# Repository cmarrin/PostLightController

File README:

To send PostLightController board to seeedstudio (https://www.seeedstudio.com/fusion_pcb.html):

	1) open PostLightController.kicad_pcb

	2) go to File->Plot...

	3) Make sure Use Extended X2 Format is not checked

	4) Make sure Output folder is 'gbr/'

	5) Press Plot to generate all the files

	6) Press Generate Drill Files...

	7) Press Generate Drill Files on the sheet that comes up

	8) Go to console in the PostLightController directory and run 'zip PostLightController-gbr.zip gbr/*'

	9) Upload the resulting PostLightController-gbr.zip to SeeedStudio

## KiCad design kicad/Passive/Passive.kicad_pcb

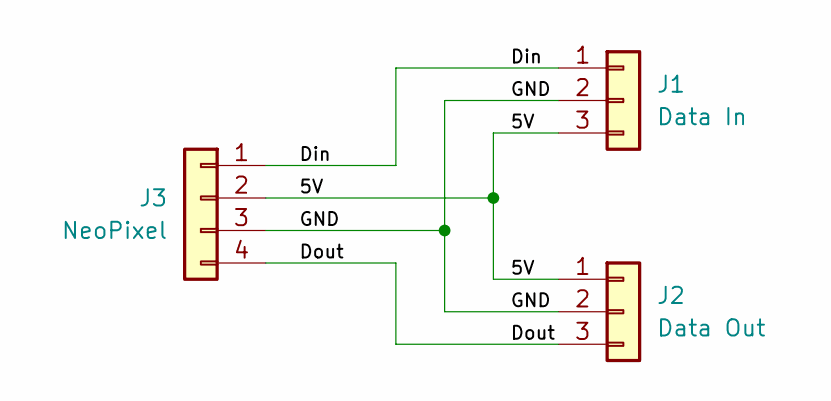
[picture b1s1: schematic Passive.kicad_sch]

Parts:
J1: Data In; PinHeader_1x03_P2.54mm_Horizontal
J2: Data Out; PinHeader_1x03_P2.54mm_Horizontal
J3: NeoPixel; PinHeader_1x04_P2.54mm_Horizontal

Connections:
/5V: J1.3, J2.1, J3.2
/Din: J1.1, J3.1
/Dout: J2.3, J3.4
/GND: J1.2, J2.2, J3.3

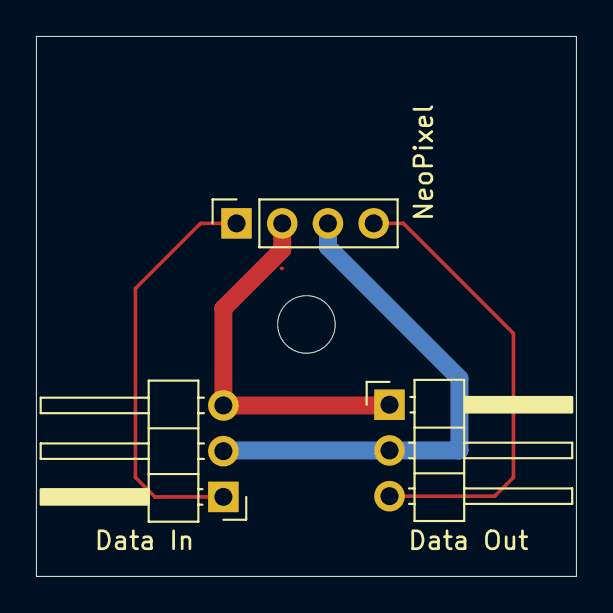
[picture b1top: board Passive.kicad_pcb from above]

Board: 2 copper layers, 30.0 x 30.0 mm, 3 parts (0 on the bottom side), 4 nets.

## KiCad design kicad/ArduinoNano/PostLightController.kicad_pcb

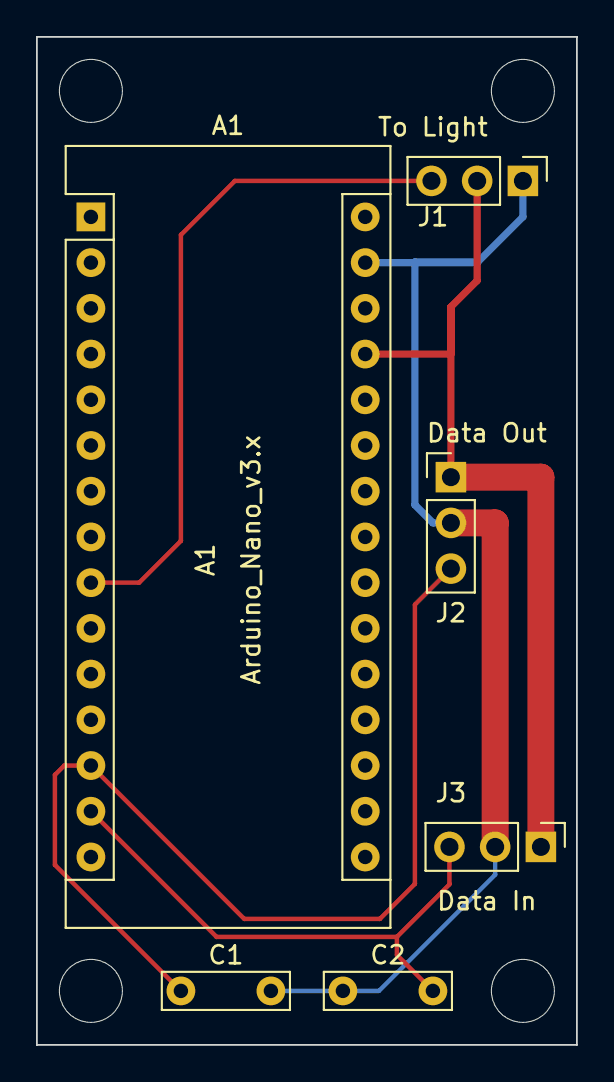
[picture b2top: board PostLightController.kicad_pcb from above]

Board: 2 copper layers, 30.0 x 56.0 mm, 6 parts (0 on the bottom side), 5 nets.

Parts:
A1: Arduino_Nano_v3.x; Arduino_Nano
C1, C2: C; C_Rect_L7.0mm_W2.0mm_P5.00mm
J1: To Light; Pin_Header_Straight_1x03_Pitch2.54mm
J2: Data Out; Pin_Header_Straight_1x03_Pitch2.54mm
J3: Data In; Pin_Header_Straight_1x03_Pitch2.54mm

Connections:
unnamed: A1.9, J1.3
unnamed: A1.13, C1.1, J2.3
unnamed: A1.14, C2.1, J3.3
unnamed: A1.27, J1.2, J2.1, J3.1
unnamed: A1.29, C1.2, C2.2, J1.1, J2.2, J3.2

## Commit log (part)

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2022-01-29 Added scanning of 2 character op sequences for Clover compiler
2022-01-30 Changed Arly syntax
    init and loop keywords are gone. At the end of the file is a lit of effects. As before they have the keyword effect, a single character name and the number of params. But added is an identifier of an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
2022-01-30 Add a Return to the end of functions so they know when to stop
2022-01-30 Renamed LoadIX/StoreIX to LoadDeref/StoreDeref
    This is in preparation for replacing all the indexed instructions with LoadRef/LoadDeref/StoreDeref.
2022-01-30 Got rid of unused OpParams
2022-02-01 Changed LoadParam call to use Rd rather than R
    There's no reason to put the LoadParam register in the lower 2 bits. You need the extra byte anyway, so just moving it there.
2022-02-01 Added unary inc and dec, for later use
2022-02-01 Minor updates to Clover source file
2022-02-01 Added documentation for RAM and Temp sizes in executable
2022-02-02 Added ability to ignore newlines in Scanner
2022-02-03 Fixed lights not coming on in Flicker
    Wasn't initing the array for a long enough length
2022-02-04 WIP - starting to generate code for Clover
    I've setup the stack and can find globals, constants and locals, including formal params. Generating code for loading of symbols, but not yet generating any ops.
2022-02-04 Fixed a bug in Arly compiler
    Arly test now runs as before
2022-02-06 Added Push and Pop opcodes
2022-02-07 Got simple Clover test case working
    Still some work to do with error checking. But this simple test works
2022-02-07 Switched Arly test to use new native functions
2022-02-07 Replaced built-in SetLight and Animate opcodes with NativeFunction versions
    Added these to Arly test case. Everything works on Arduino with the Arly code
2022-02-10 Moved all interpreter stack access to Stack class
    This gives better control over stack variables and allows more error checking
2022-02-10 Fixed some issues with Arduino build
2022-02-13 Fixed bug in Call code storage
    The opcode was wrong. So I moved Call to the above 0x80 range and allowed it to have 4 upper bits as well as the lower bits in the next byte
2022-02-13 WIP - grammar was wrong and now its starting to work
    - I had the grammar wrong for chained operations. You could not have 'a[i].b' because you couldn't chain postfix operations. That's all fixed now.
    - That chain operation and others now work.
    - Started getting binary operations to work. Still need to complete the work and add logic for the rest of the operators
    - Currently always generating ops for Int binary operations, which is wrong. Need to determine type of right and left sides and do error handling
    - Next I will separate out assignment operators from the other. I won't be supporting chained assignment.
2022-02-13 Got function calls working
2022-02-13 Added support for a return type on functions
    Type is optional. If omitted, return type is None and you can't return a value
2022-02-14 Added charno support
    Now Error output includes charno as well as lineno
2022-02-14 Fixed bug handing precedence
2022-02-14 Made values in table floats
2022-02-14 Added more native functions and restructured handling
    Added logging and random functions. Simplified native function handling logic since we're getting so many
2022-02-14 Fixed param passing to Log functions
2022-02-15 Added InitArray native function
2022-02-15 Finished up SetFrame handling
2022-02-15 Got if statement working and other type related fixes
    Now the 'f' command works. All commands in clvr file work now
2022-02-15 Got rid of local variable shadowing formal param
2022-02-15 Push a return value in Arly so the stack works
2022-02-15 Changed Arly to use NativeFunction Int
2022-02-15 Got rid of Min and Max opcodes and added native function replacements
2022-02-15 Change handleFunction name to return Function ref so we can use it later
2022-02-17 Got rid of Log ops and removed unused param from Log native calls
2022-02-17 Added annotation support
    An annotation is a string of one line of code and a 32 bit integer. The integer is either -1, meaning this line doesn't have an address associated with it. Or it is an address in the code. When the d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
2022-02-17 More changes for new log api
2022-02-17 Added handling of unary operators ('-', '~' and '!')
2022-02-17 Added try/catch to Compiler to catch throws on Emit
2022-02-17 Added 'm' effect
    You pass 4 colors and a duration. Each color fades in, displays for duration seconds and then fades out and the next color fades in.
2022-02-20 Added RandomSeed to Mac and Arduino
2022-02-21 Got rid of PushZero
    Not needed now that we have a 1 byte constant push (PushIntConstS)
2022-02-22 Got rid of automatic minus handling for numeric constants
    This made it impossible to handle '--' properly. Doing it as a unary Neg op only adds a byte and this way we can handle constants from 0-15 in the PushIntConstS op
2022-02-22 WIP - Moved files around into new structure so I can make them into a library
    I nuked all the color specific native functions so nothing works. But I'll put it all back together shortly. And Arduino won't work anymore
2022-02-23 Added a dummy Clover.h
    This just includes interpreter.h. This makes it so you can #include <Clover.h> in Arduino for clarity
2022-02-23 Moved files into Clover
2022-02-23 Getting rid of Clover
    It's in a new repo now
2022-02-23 Renamed mac project to CompileClover
2022-02-24 Fiddled some Mac files
2022-02-26 synced Clover
2022-02-27 Changed main to send string command rather than char
    Commands are still 1 char. But now they could be more
2022-02-28 Added support for non-segmented binary files and .h formatted data files
    You can now write binary output as a single file. You can also output a .h file with the binary data represented as hex bytes. This will all a sketch to be written that will compile in the binary so 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
2022-03-02 Got rid of some derived data
2022-03-10 Updated Clover version
2022-03-10 Renamed Mac project
2022-03-10 Added Rainbow effect
    Goes through the rainbow of colors by animating hue
2022-03-21 Updated to latest Clover
2022-03-29 Updated scripts for new for functionality
2023-12-31 Change baud rate to 300
2024-01-01 Fixed bugs in keeping track of payload size
    Renamed some vars to make it more clear what we're keeping track of. Now all commands and executable upload all work
2024-01-01 Changed sprintf to snprintf because latter is deprecated
2024-01-24 Change baud rate to 1200
    Node-red has a bug where it can't send serial at any speed less than 1200
2024-01-24 More of passthrough checksum fix
2024-03-03 Changes to effects
    Flicker has a better range now. And all effects handle incoming brightness
2024-06-04 Experimenting with Formatter
2024-09-06 Got rid of Clover
2025-06-04 Switched to new PostLightController logic
    This was developed as part of the Clover project and ported over here.
2025-06-07 WIP - Added PostLightControllerESP.ino
    This will be the ESP WiFi based PostLightController
2025-06-11 Moved things around
2025-06-11 Added HTTP handlers for commands and upload
    For the ESP sending an HTTP request will send commands. For instance sending to 'http://host/command?cmd=C123456' will send the C command. I also added a /update request which will handle POST to upl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
2025-06-23 Change from using Serial directly to using cout
2025-06-25 Fixed a print
2025-06-25 Got Mac simulator working
    Wait until effect is finished before sending command to simulate. This lets the initial flash finish first.
    Only loop 20 times so we don't go forever
2025-06-26 Moved uploadExecutable to common PostLightController class
    Eventually both Mac and ESP will store the executable in the WebFIleSystem. For now is just stores it in a block of RAM
2025-06-26 Changed startup message
2025-06-26 Added sample data file for LittleFS upload.
    This gets uploaded to the device using the instructions here: https://randomnerdtutorials.com/arduino-ide-2-install-esp32-littlefs/#installing-MAC
2025-06-30 Updated to new way of accessing executable
    Now FS is used to load executable and a static function is used to give access to it to the Interpreter
2025-06-30 Changed custom partitions file
    Looks like the SPIFFS partition (used for LittleFS) needs to be on a coarser boundary than I had it.
2025-06-30 Ignore upload data
2025-07-01 Added support for built in Color command
2025-07-08 Changed SetAllLights to SetLights to set a range of lights
2025-07-08 Added some status lights
2025-07-08 Moved executable load to its own function
    After upload I was not loading the resultant executable.
2025-07-10 Changed animate() slightly to avoid any overflow
2025-07-10 Fixed a bug passing value to initFade
    I was passing multiColorIndex rather than multiColorIndex[post] which had the effect of always initializing the first fade values
2025-08-30 WIF - Get rid of cout everywhere
2025-08-30 Got rid of old file
2025-09-13 Got working with WiFiPortal.
    Mac and Arduino basically work.
2025-09-15 Add a delay after serial init so early prints show up
2025-09-24 getHTTPArg is no longer static
2025-10-01 Added testing for Lua
2025-10-02 Changed WiFiPortal API a bit
    It is now in the mil namespace, and the request handler now just takes a WiFiPortal pointer and returns void
2025-10-12 Added WebShell to the build
2025-10-12 Updates to builds so ESPlib can be an included project
2025-10-13 Removed Lua from build
    It's now in a project of its own
2026-04-05 Added tigr submodule
2026-04-05 Initial checkin of espidf files for PostLightController
    Not working yet
2026-04-05 Made setTitle use proper Version define
2026-04-05 Changed espidf main.cpp to the right one
2026-04-07 System is now in mil namespace where it belongs
2026-04-07 Got Flash using hsv properly.
    Now the start color is really green and I can set the color using curl to send an HTTP request and get the desired color set (for the 'C' command)
2026-04-07 Fixed a bug in string handling
    This is yet another example of string.length() giving back a length that includes the terminating null
2026-04-09 Turn off the LEDs at startup in case they were left on
2026-04-09 Added condition_variable to sync tigrUpdate with LED rendering
    Before tigrUpdate could happen in the middle of rendering the LED rings. This would cause flickering. Now I finish the render of the rings and then wait for tigrUpdate to finish. I make sure that we'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
2026-04-20 Got rid of old cruft from project file
2026-04-20 Moved espidf to PostLightController-espidf
    When you give the espidf top-level folder a generic name like this it makes it very confusing which project you're in when you use VSCode
2026-04-28 Got rid of the no longer existent linenoise.c
2026-05-01 Moved tigrUpdate out of if (needsRender) to avoid the SPOD in the render window
2026-05-02 Trying to set bundle identifier to get a warning to go away.
    Didn't work, oh well
2026-05-10 Added error checking to parseCmd and constrain the range of numeric params
2026-05-17 Made Flicker program obey incoming brightness
2026-05-18 Changed how render sync works on Mac
    Now I simply have a render flag so the main thread knows when to call tigrUpdate(). The render thread keeps the mutex locked while it's rendering and the main thread keeps it locks when it calls tigr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
2026-05-27 Renamed mainpanel to uipanel
2026-05-28 Some updates for new version of XCode
2026-06-06 Added Flicker.lua to project
2026-06-12 Updated name of JSONParser
